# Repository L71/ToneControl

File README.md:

ToneControl
===========

Eurorack dual audio input amplifier and "tilt" type tone control. 
Input 2 is normalized to the unprocessed output of the ch1 amplifier. 

Tone control circuit from http://sound.whsites.net/articles/eq.htm#s10

Panels and PCBs licensed cc-by-sa.

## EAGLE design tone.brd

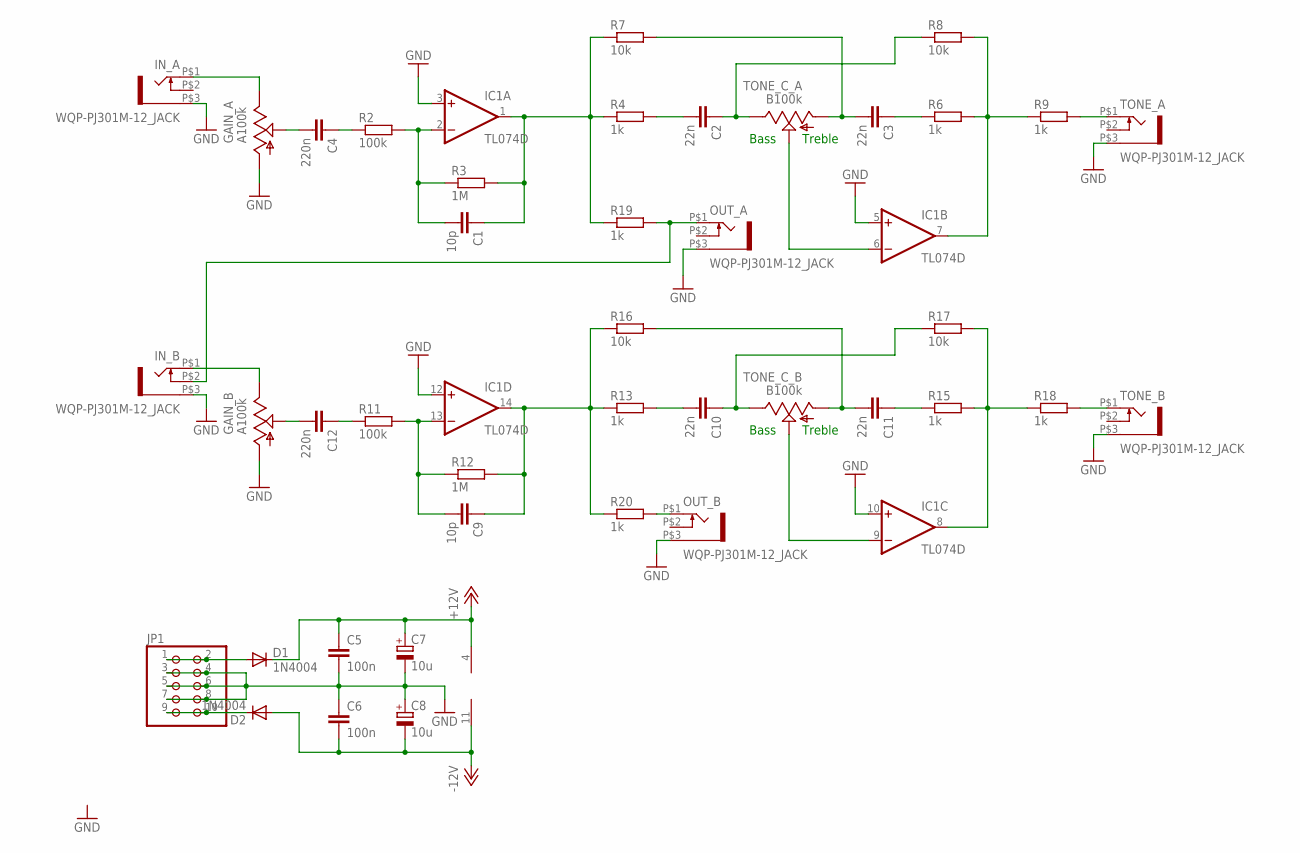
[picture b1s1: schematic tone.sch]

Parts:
C1, C9: 10p; C0603K
C2, C3, C10, C11: 22n; C050-025X075
C4, C12: 220n; C050-025X075
C5, C6: 100n; C025-025X050
C7, C8: 10u; E2,5-6
D1, D2: 1N4004; DO41-10
GAIN_A: A100k; ALPS_POT_VERTICAL
GAIN_B: A100k; ALPS_POT_VERTICAL
IC1: TL074D; SO14
IN_A: WQP-PJ301M-12_JACK
IN_B: WQP-PJ301M-12_JACK
JP1: PINHD-2X5; 2X05
OUT_A: WQP-PJ301M-12_JACK
OUT_B: WQP-PJ301M-12_JACK
R2, R11: 100k; R0603
R3, R12: 1M; R0603
R4, R6, R9, R13, R15, R18, R19, R20: 1k; R0603
R7, R8, R16, R17: 10k; R0603
TONE_A: WQP-PJ301M-12_JACK
TONE_B: WQP-PJ301M-12_JACK
TONE_C_A: B100k; ALPS_POT_VERTICAL
TONE_C_B: B100k; ALPS_POT_VERTICAL

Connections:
+12V: C5.1, C7.+, D1.C, IC1.4 (V+)
-12V: C6.2, C8.-, D2.A, IC1.11 (V-)
GND: C5.2, C6.1, C7.-, C8.+, GAIN_A.P$3 (A), GAIN_B.P$3 (A), IC1.3 (+IN), IC1.5 (+IN), IC1.10 (+IN), IC1.12 (+IN), IN_A.P$3 (1), IN_B.P$3 (1), JP1.3, JP1.4, JP1.5, JP1.6, JP1.7, JP1.8, OUT_A.P$3 (1), OUT_B.P$3 (1), TONE_A.P$3 (1), TONE_B.P$3 (1)
unnamed: C1.1, IC1.1 (OUT), R3.2, R4.1, R7.1, R19.1
unnamed: C4.2, GAIN_A.P$2 (S)
unnamed: C2.2, R4.2
unnamed: C2.1, R8.1, TONE_C_A.P$1 (E)
unnamed: C3.2, R7.2, TONE_C_A.P$3 (A)
unnamed: C3.1, R6.1
unnamed: IC1.7 (OUT), R6.2, R8.2, R9.1
unnamed: C4.1, R2.1
unnamed: IC1.6 (-IN), TONE_C_A.P$2 (S)
unnamed: C1.2, IC1.2 (-IN), R2.2, R3.1
unnamed: D1.A, JP1.1, JP1.2
unnamed: GAIN_A.P$1 (E), IN_A.P$1 (2)
unnamed: R9.2, TONE_A.P$1 (2)
unnamed: D2.C, JP1.9, JP1.10
unnamed: C9.1, IC1.14 (OUT), R12.2, R13.1, R16.1, R20.1
unnamed: C10.2, R13.2
unnamed: C10.1, R17.1, TONE_C_B.P$1 (E)
unnamed: C11.2, R16.2, TONE_C_B.P$3 (A)
unnamed: C11.1, R15.1
unnamed: IC1.8 (OUT), R15.2, R17.2, R18.1
unnamed: C9.2, IC1.13 (-IN), R11.2, R12.1
unnamed: C12.2, GAIN_B.P$2 (S)
unnamed: C12.1, R11.1
unnamed: GAIN_B.P$1 (E), IN_B.P$1 (2)
unnamed: R18.2, TONE_B.P$1 (2)
unnamed: IC1.9 (-IN), TONE_C_B.P$2 (S)
unnamed: IN_B.P$2 (3), OUT_A.P$1 (2), R19.2
unnamed: OUT_B.P$1 (2), R20.2

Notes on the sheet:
Bass
Treble

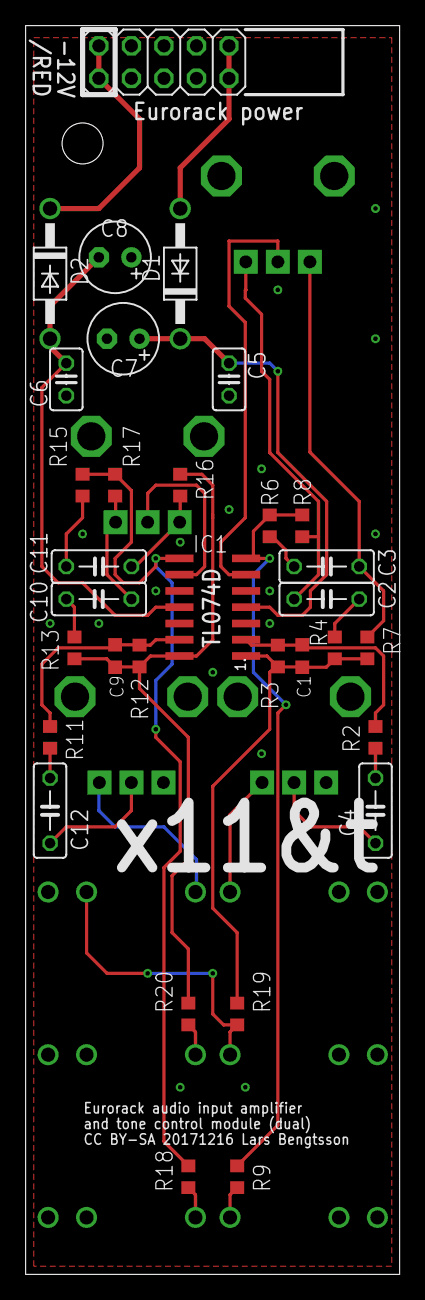
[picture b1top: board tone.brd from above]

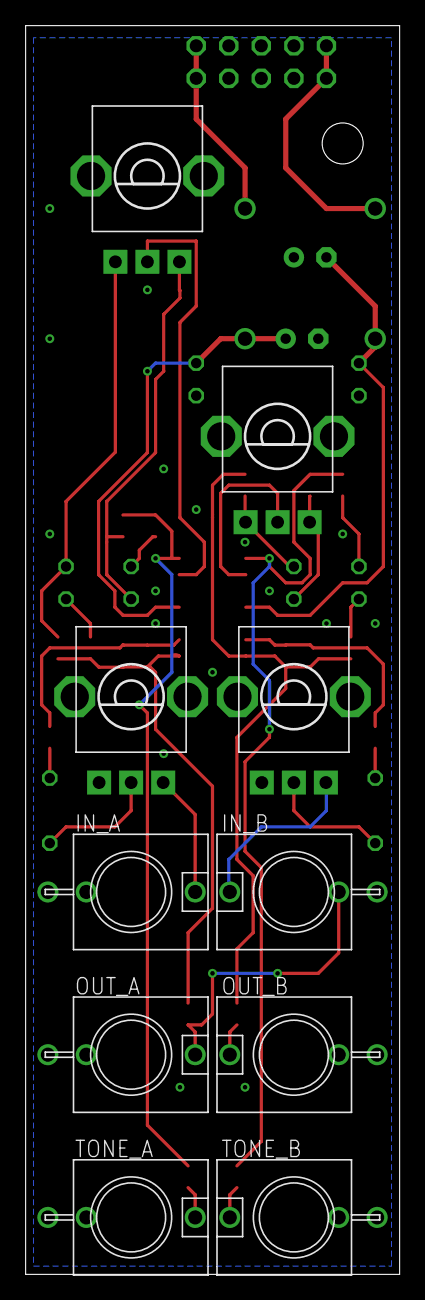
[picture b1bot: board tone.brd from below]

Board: 2 copper layers, 29.2 x 97.5 mm, 42 parts (10 on the bottom side), 31 nets.

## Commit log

2017-12-21 Initial commit.
2018-01-07 Rotated & rerouted a few resistors. Simpler to solder board if all are in one direction. Added type label & pin 1 indicator for IC1.

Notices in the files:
tone.brd:
CC BY-SA 20171216 Lars Bengtsson
